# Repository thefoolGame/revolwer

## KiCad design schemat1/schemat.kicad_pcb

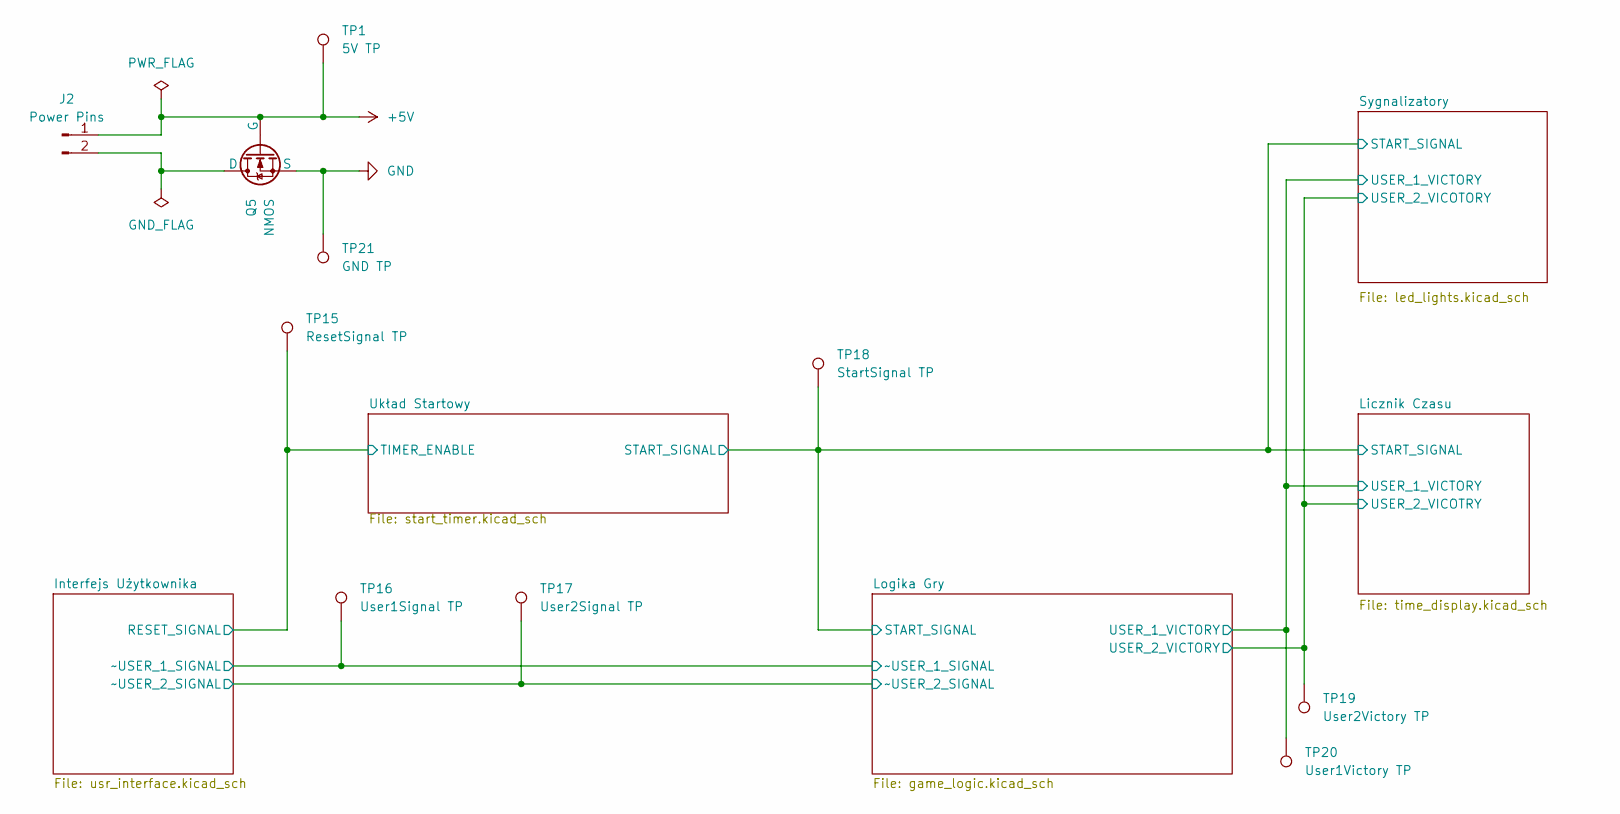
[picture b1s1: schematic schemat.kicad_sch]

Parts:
J2: Power Pins; Molex_KK-254_AE-6410-02A_1x02_P2.54mm_Vertical
Q5: NMOS; TO-220-3_Vertical
TP1: 5V TP; PinHeader_1x01_P2.54mm_Vertical
TP15: ResetSignal TP; PinHeader_1x01_P2.54mm_Vertical
TP16: User1Signal TP; PinHeader_1x01_P2.54mm_Vertical
TP17: User2Signal TP; PinHeader_1x01_P2.54mm_Vertical
TP18: StartSignal TP; PinHeader_1x01_P2.54mm_Vertical
TP19: User2Victory TP; PinHeader_1x01_P2.54mm_Vertical
TP20: User1Victory TP; PinHeader_1x01_P2.54mm_Vertical
TP21: GND TP; PinHeader_1x01_P2.54mm_Vertical

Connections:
+5V: J2.1, Q5.2 (G), TP1.1; also elsewhere on the board
/Interfejs Użytkownika/RESET_SIGNAL: TP15.1; also elsewhere on the board
/Interfejs Użytkownika/~USER_1_SIGNAL: TP16.1; also elsewhere on the board
/Interfejs Użytkownika/~USER_2_SIGNAL: TP17.1; also elsewhere on the board
/Licznik Czasu/START_SIGNAL: TP18.1; also elsewhere on the board
/Licznik Czasu/USER_1_VICTORY: TP20.1; also elsewhere on the board
/Licznik Czasu/USER_2_VICOTRY: TP19.1; also elsewhere on the board
GND: Q5.3 (S), TP21.1; also elsewhere on the board
unnamed: J2.2, Q5.1 (D)

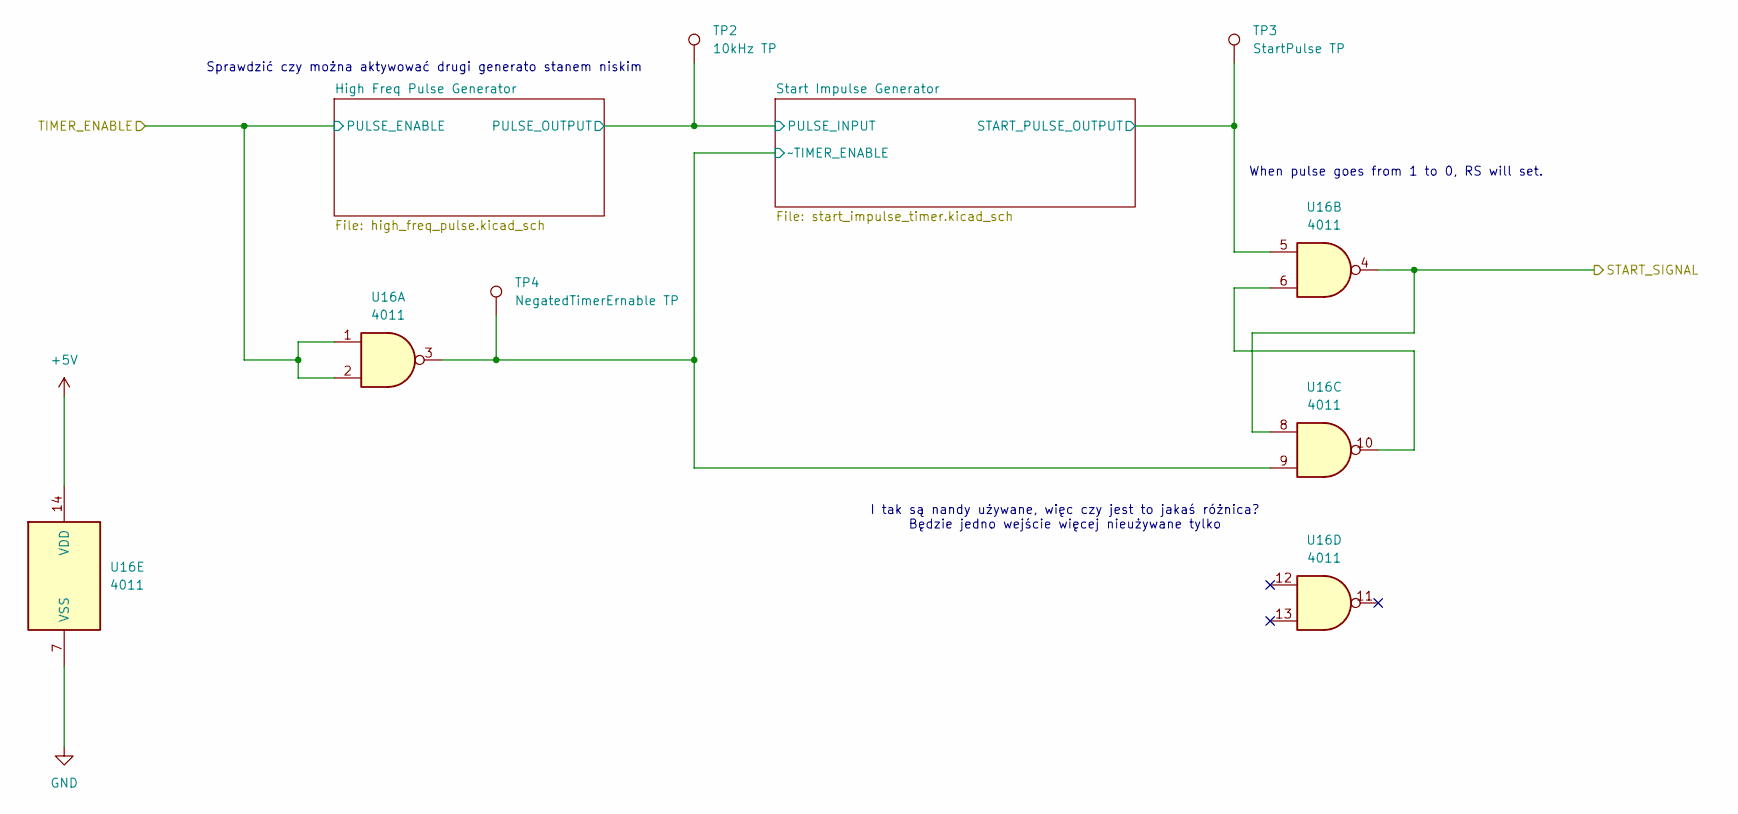
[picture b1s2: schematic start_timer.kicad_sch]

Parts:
TP2: 10kHz TP; PinHeader_1x01_P2.54mm_Vertical
TP3: StartPulse TP; PinHeader_1x01_P2.54mm_Vertical
TP4: NegatedTimerErnable TP; PinHeader_1x01_P2.54mm_Vertical
U16: 4011; DIP-14_W7.62mm

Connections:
+5V: U16.14 (VDD); also elsewhere on the board
/Interfejs Użytkownika/RESET_SIGNAL: U16.1, U16.2; also elsewhere on the board
/Licznik Czasu/START_SIGNAL: U16.4, U16.8; also elsewhere on the board
/Układ Startowy/High Freq Pulse Generator/PULSE_OUTPUT: TP2.1; also elsewhere on the board
/Układ Startowy/Start Impulse Generator/START_PULSE_OUTPUT: TP3.1, U16.5; also elsewhere on the board
/Układ Startowy/Start Impulse Generator/~TIMER_ENABLE: TP4.1, U16.3, U16.9; also elsewhere on the board
GND: U16.7 (VSS); also elsewhere on the board
unnamed: U16.6, U16.10

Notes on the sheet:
I tak są nandy używane, więc czy jest to jakaś różnica? Będzie jedno wejście więcej nieużywane tylko
Sprawdzić czy można aktywować drugi generato stanem niskim
When pulse goes from 1 to 0, RS will set.

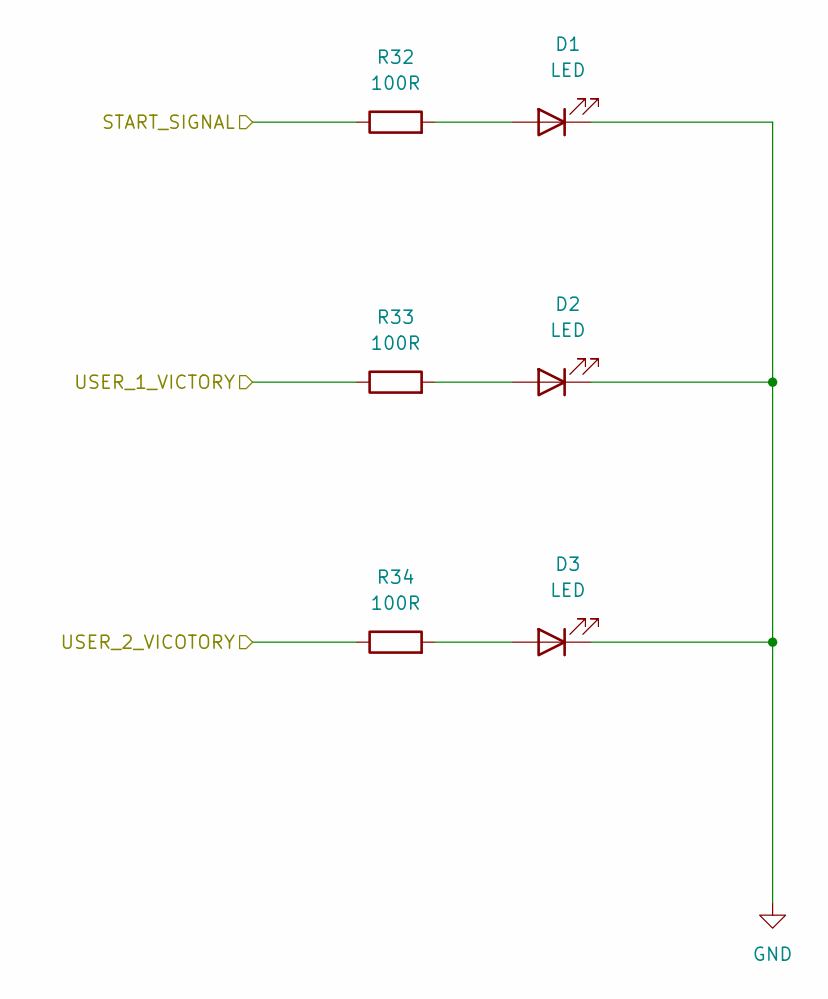
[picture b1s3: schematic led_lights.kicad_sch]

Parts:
D1, D2, D3: LED; LED_D4.0mm
R32, R33, R34: 100R; R_Axial_DIN0207_L6.3mm_D2.5mm_P10.16mm_Horizontal

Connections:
/Licznik Czasu/START_SIGNAL: R32.1; also elsewhere on the board
/Licznik Czasu/USER_1_VICTORY: R33.1; also elsewhere on the board
/Licznik Czasu/USER_2_VICOTRY: R34.1; also elsewhere on the board
GND: D1.1 (K), D2.1 (K), D3.1 (K); also elsewhere on the board
unnamed: D1.2 (A), R32.2
unnamed: D2.2 (A), R33.2
unnamed: D3.2 (A), R34.2

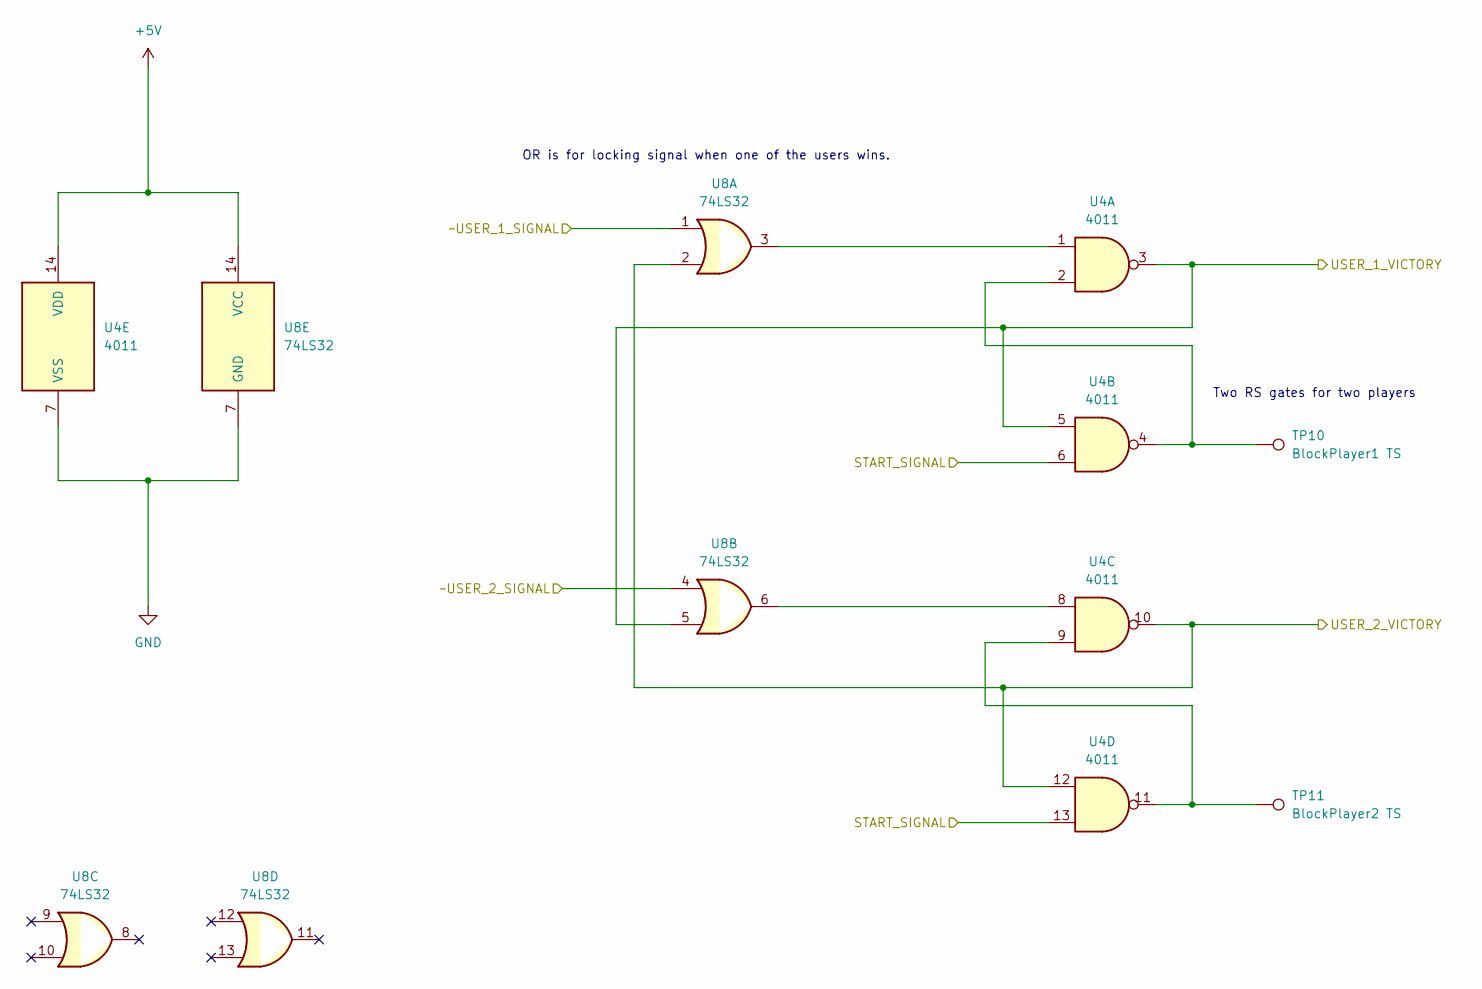
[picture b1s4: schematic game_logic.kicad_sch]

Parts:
TP10: BlockPlayer1 TS; PinHeader_1x01_P2.54mm_Vertical
TP11: BlockPlayer2 TS; PinHeader_1x01_P2.54mm_Vertical
U4: 4011; DIP-14_W7.62mm
U8: 74LS32; DIP-14_W7.62mm

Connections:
+5V: U4.14 (VDD), U8.14 (VCC); also elsewhere on the board
/Interfejs Użytkownika/~USER_1_SIGNAL: U8.1; also elsewhere on the board
/Interfejs Użytkownika/~USER_2_SIGNAL: U8.4; also elsewhere on the board
/Licznik Czasu/START_SIGNAL: U4.6, U4.13; also elsewhere on the board
/Licznik Czasu/USER_1_VICTORY: U4.3, U4.5, U8.5; also elsewhere on the board
/Licznik Czasu/USER_2_VICOTRY: U4.10, U4.12, U8.2; also elsewhere on the board
GND: U4.7 (VSS), U8.7 (GND); also elsewhere on the board
unnamed: TP10.1, U4.2, U4.4
unnamed: TP11.1, U4.9, U4.11
unnamed: U4.1, U8.3
unnamed: U4.8, U8.6

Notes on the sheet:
OR is for locking signal when one of the users wins.
Two RS gates for two players

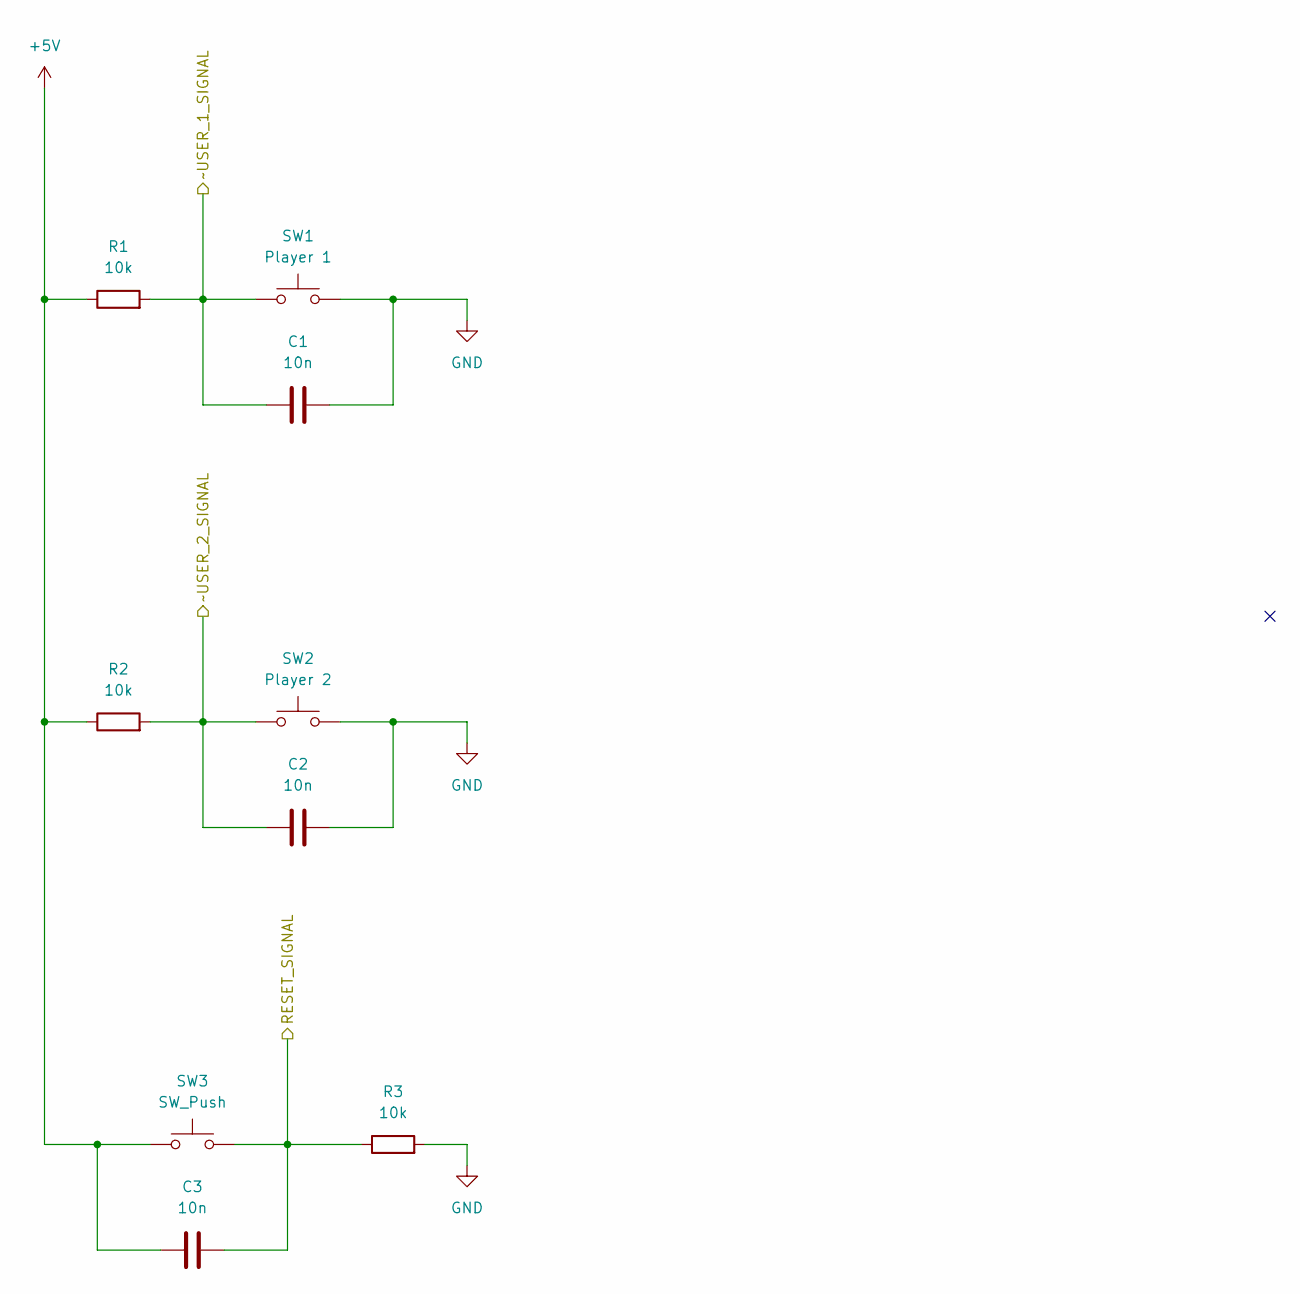
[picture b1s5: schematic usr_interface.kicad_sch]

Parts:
C1, C2, C3: 10n; C_Disc_D3.4mm_W2.1mm_P2.50mm
R1, R2, R3: 10k; R_Axial_DIN0207_L6.3mm_D2.5mm_P10.16mm_Horizontal
SW1: Player 1; SW_PUSH_6mm_H5mm
SW2: Player 2; SW_PUSH_6mm_H5mm
SW3: SW_Push; SW_PUSH_6mm_H5mm

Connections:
+5V: C3.1, R1.1, R2.1, SW3.1; also elsewhere on the board
/Interfejs Użytkownika/RESET_SIGNAL: C3.2, R3.1, SW3.2; also elsewhere on the board
/Interfejs Użytkownika/~USER_1_SIGNAL: C1.1, R1.2, SW1.1; also elsewhere on the board
/Interfejs Użytkownika/~USER_2_SIGNAL: C2.1, R2.2, SW2.1; also elsewhere on the board
GND: C1.2, C2.2, R3.2, SW1.2, SW2.2; also elsewhere on the board

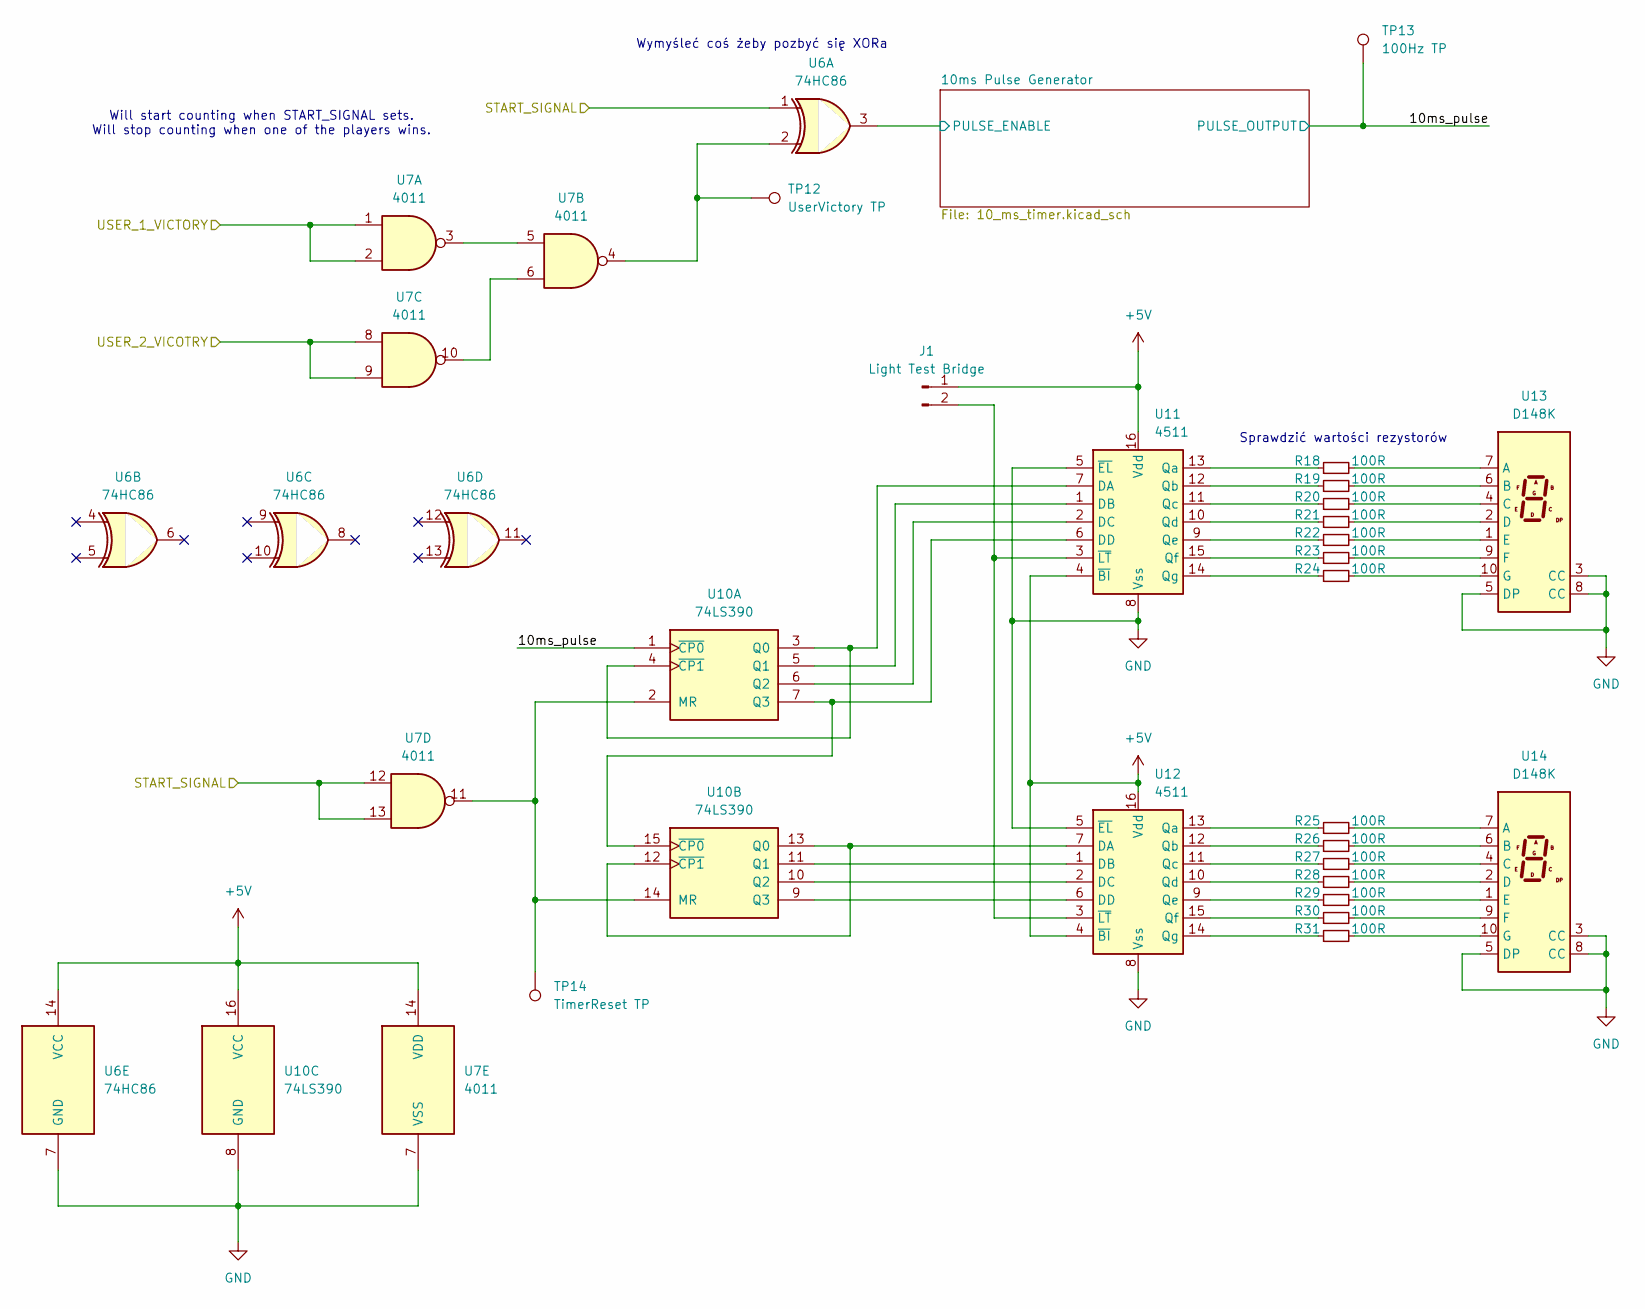
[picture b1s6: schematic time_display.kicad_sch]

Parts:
J1: Light Test Bridge; PinHeader_1x02_P2.54mm_Vertical
R18, R19, R20, R21, R22, R23, R24, R25, R26, R27, R28, R29, R30, R31: 100R; R_Axial_DIN0207_L6.3mm_D2.5mm_P10.16mm_Horizontal
TP12: UserVictory TP; PinHeader_1x01_P2.54mm_Vertical
TP13: 100Hz TP; PinHeader_1x01_P2.54mm_Vertical
TP14: TimerReset TP; PinHeader_1x01_P2.54mm_Vertical
U6: 74HC86; DIP-14_W7.62mm
U7: 4011; DIP-14_W7.62mm
U10: 74LS390; DIP-16_W7.62mm
U11, U12: 4511; DIP-16_W7.62mm
U13, U14: D148K; 7SegmentLED_LTS6760_LTS6780

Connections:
+5V: J1.1, U6.14 (VCC), U7.14 (VDD), U10.16 (VCC), U11.4 (~BI), U11.16 (Vdd), U12.4 (~BI), U12.16 (Vdd); also elsewhere on the board
/Licznik Czasu/10ms Pulse Generator/PULSE_ENABLE: U6.3; also elsewhere on the board
/Licznik Czasu/10ms_pulse: TP13.1, U10.1 (~CP0); also elsewhere on the board
/Licznik Czasu/START_SIGNAL: U6.1, U7.12, U7.13; also elsewhere on the board
/Licznik Czasu/USER_1_VICTORY: U7.1, U7.2; also elsewhere on the board
/Licznik Czasu/USER_2_VICOTRY: U7.8, U7.9; also elsewhere on the board
GND: U6.7 (GND), U7.7 (VSS), U10.8 (GND), U11.5 (~EL), U11.8 (Vss), U12.5 (~EL), U12.8 (Vss), U13.3 (CC), U13.5 (DP), U13.8 (CC), U14.3 (CC), U14.5 (DP), U14.8 (CC); also elsewhere on the board
unnamed: J1.2, U11.3 (~LT), U12.3 (~LT)
unnamed: TP12.1, U6.2, U7.4
unnamed: U7.3, U7.5
unnamed: U7.6, U7.10
unnamed: TP14.1, U7.11, U10.2 (MR), U10.14 (MR)
unnamed: U10.3 (Q0), U10.4 (~CP1), U11.7 (DA)
unnamed: U10.5 (Q1), U11.1 (DB)
unnamed: U10.6 (Q2), U11.2 (DC)
unnamed: U10.7 (Q3), U10.15 (~CP0), U11.6 (DD)
unnamed: U10.12 (~CP1), U10.13 (Q0), U12.7 (DA)
unnamed: U10.11 (Q1), U12.1 (DB)
unnamed: U10.10 (Q2), U12.2 (DC)
unnamed: U10.9 (Q3), U12.6 (DD)
unnamed: R18.1, U11.13 (Qa)
unnamed: R19.1, U11.12 (Qb)
unnamed: R20.1, U11.11 (Qc)
unnamed: R21.1, U11.10 (Qd)
unnamed: R22.1, U11.9 (Qe)
unnamed: R23.1, U11.15 (Qf)
unnamed: R24.1, U11.14 (Qg)
unnamed: R25.1, U12.13 (Qa)
unnamed: R26.1, U12.12 (Qb)
unnamed: R27.1, U12.11 (Qc)
unnamed: R28.1, U12.10 (Qd)
unnamed: R29.1, U12.9 (Qe)
unnamed: R30.1, U12.15 (Qf)
unnamed: R31.1, U12.14 (Qg)
unnamed: R18.2, U13.7 (A)
unnamed: R19.2, U13.6 (B)
unnamed: R20.2, U13.4 (C)
unnamed: R21.2, U13.2 (D)
unnamed: R22.2, U13.1 (E)
unnamed: R23.2, U13.9 (F)
unnamed: R24.2, U13.10 (G)
unnamed: R25.2, U14.7 (A)
unnamed: R26.2, U14.6 (B)
unnamed: R27.2, U14.4 (C)
unnamed: R28.2, U14.2 (D)
unnamed: R29.2, U14.1 (E)
unnamed: R30.2, U14.9 (F)
unnamed: R31.2, U14.10 (G)

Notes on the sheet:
Will start counting when START_SIGNAL sets. Will stop counting when one of the players wins.
Sprawdzić wartości rezystorów
Wymyśleć coś żeby pozbyć się XORa

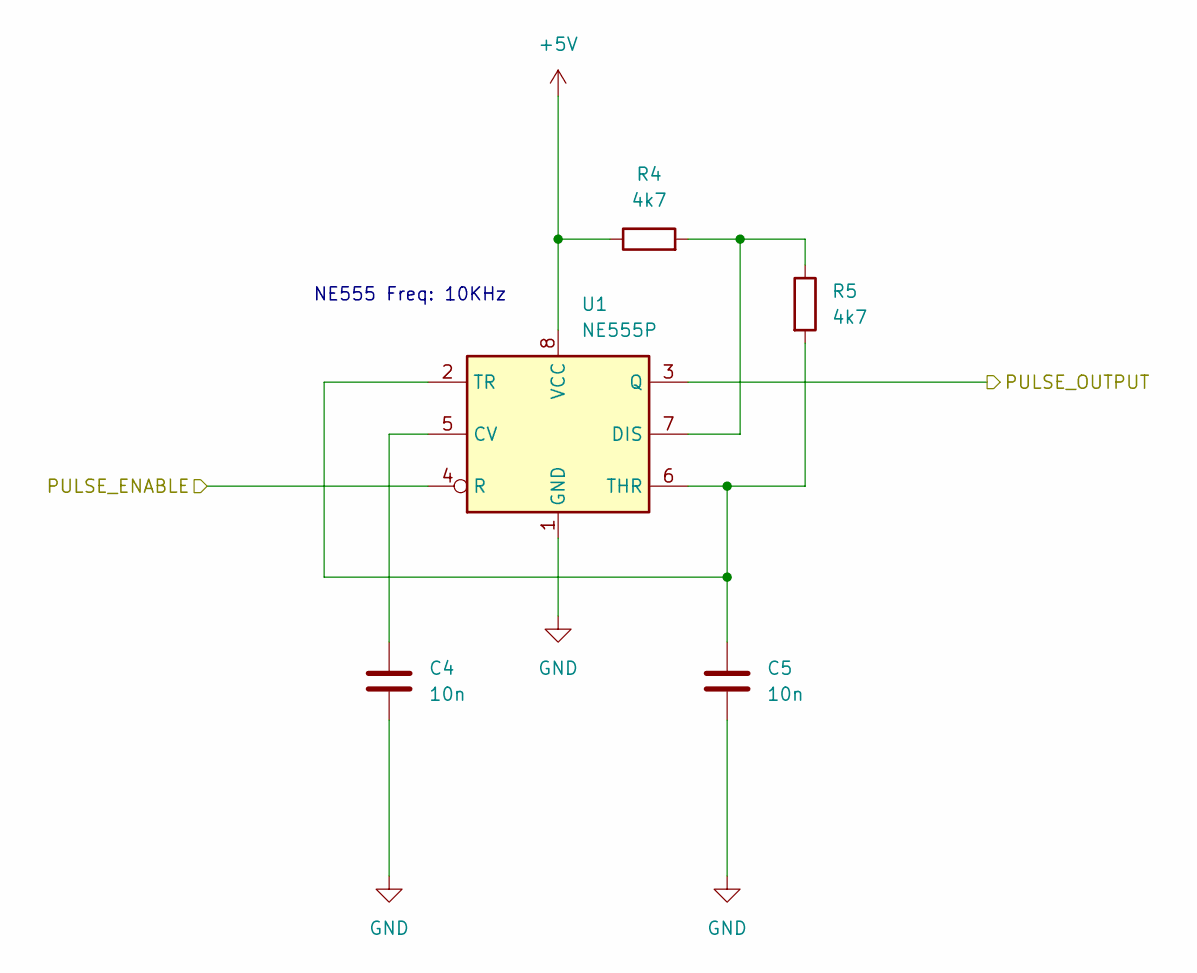
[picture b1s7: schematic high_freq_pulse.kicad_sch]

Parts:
C4, C5: 10n; C_Disc_D3.4mm_W2.1mm_P2.50mm
R4, R5: 4k7; R_Axial_DIN0207_L6.3mm_D2.5mm_P10.16mm_Horizontal
U1: NE555P; DIP-8_W7.62mm

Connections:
+5V: R4.1, U1.8 (VCC); also elsewhere on the board
/Interfejs Użytkownika/RESET_SIGNAL: U1.4 (R); also elsewhere on the board
/Układ Startowy/High Freq Pulse Generator/PULSE_OUTPUT: U1.3 (Q); also elsewhere on the board
GND: C4.2, C5.2, U1.1 (GND); also elsewhere on the board
unnamed: C4.1, U1.5 (CV)
unnamed: R4.2, R5.1, U1.7 (DIS)
unnamed: C5.1, R5.2, U1.2 (TR), U1.6 (THR)

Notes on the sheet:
NE555 Freq: 10KHz

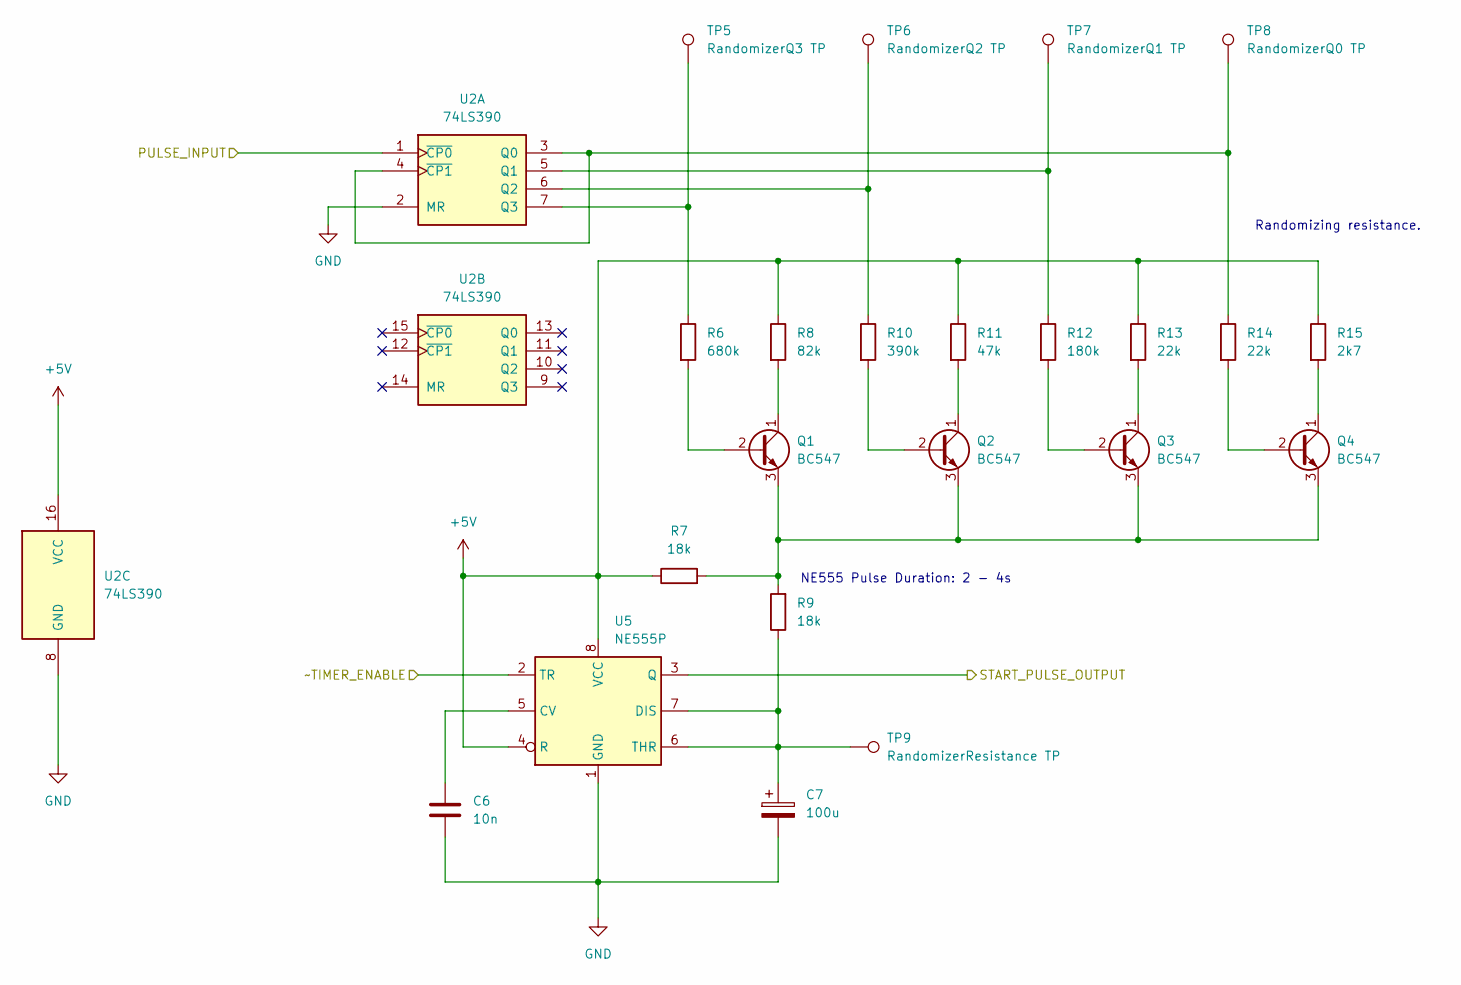
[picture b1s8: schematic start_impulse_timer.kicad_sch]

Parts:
C6: 10n; C_Disc_D3.4mm_W2.1mm_P2.50mm
C7: 100u; CP_Radial_D6.3mm_P2.50mm
Q1, Q2, Q3, Q4: BC547; TO-92
R6: 680k; R_Axial_DIN0207_L6.3mm_D2.5mm_P10.16mm_Horizontal
R7, R9: 18k; R_Axial_DIN0207_L6.3mm_D2.5mm_P10.16mm_Horizontal
R8: 82k; R_Axial_DIN0207_L6.3mm_D2.5mm_P10.16mm_Horizontal
R10: 390k; R_Axial_DIN0207_L6.3mm_D2.5mm_P10.16mm_Horizontal
R11: 47k; R_Axial_DIN0207_L6.3mm_D2.5mm_P10.16mm_Horizontal
R12: 180k; R_Axial_DIN0207_L6.3mm_D2.5mm_P10.16mm_Horizontal
R13, R14: 22k; R_Axial_DIN0207_L6.3mm_D2.5mm_P10.16mm_Horizontal
R15: 2k7; R_Axial_DIN0207_L6.3mm_D2.5mm_P10.16mm_Horizontal
TP5: RandomizerQ3 TP; PinHeader_1x01_P2.54mm_Vertical
TP6: RandomizerQ2 TP; PinHeader_1x01_P2.54mm_Vertical
TP7: RandomizerQ1 TP; PinHeader_1x01_P2.54mm_Vertical
TP8: RandomizerQ0 TP; PinHeader_1x01_P2.54mm_Vertical
TP9: RandomizerResistance TP; PinHeader_1x01_P2.54mm_Vertical
U2: 74LS390; DIP-16_W7.62mm
U5: NE555P; DIP-8_W7.62mm

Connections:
+5V: R7.1, R8.1, R11.1, R13.1, R15.1, U2.16 (VCC), U5.4 (R), U5.8 (VCC); also elsewhere on the board
/Układ Startowy/High Freq Pulse Generator/PULSE_OUTPUT: U2.1 (~CP0); also elsewhere on the board
/Układ Startowy/Start Impulse Generator/START_PULSE_OUTPUT: U5.3 (Q); also elsewhere on the board
/Układ Startowy/Start Impulse Generator/~TIMER_ENABLE: U5.2 (TR); also elsewhere on the board
GND: C6.2, C7.2, U2.2 (MR), U2.8 (GND), U5.1 (GND); also elsewhere on the board
unnamed: Q1.2 (B), R6.2
unnamed: Q1.1 (C), R8.2
unnamed: Q1.3 (E), Q2.3 (E), Q3.3 (E), Q4.3 (E), R7.2, R9.2
unnamed: Q2.2 (B), R10.2
unnamed: Q2.1 (C), R11.2
unnamed: Q3.2 (B), R12.2
unnamed: Q3.1 (C), R13.2
unnamed: Q4.2 (B), R14.2
unnamed: Q4.1 (C), R15.2
unnamed: R14.1, TP8.1, U2.3 (Q0), U2.4 (~CP1)
unnamed: R12.1, TP7.1, U2.5 (Q1)
unnamed: R10.1, TP6.1, U2.6 (Q2)
unnamed: R6.1, TP5.1, U2.7 (Q3)
unnamed: C6.1, U5.5 (CV)
unnamed: C7.1, R9.1, TP9.1, U5.6 (THR), U5.7 (DIS)

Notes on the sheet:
Randomizing resistance.
NE555 Pulse Duration: 2 - 4s

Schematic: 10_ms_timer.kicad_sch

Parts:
C8: 10n; C_Disc_D3.4mm_W2.1mm_P2.50mm
C9: 100n; C_Disc_D6.0mm_W2.5mm_P5.00mm
R16: 44k; R_Axial_DIN0207_L6.3mm_D2.5mm_P10.16mm_Horizontal
R17: 50k; R_Axial_DIN0207_L6.3mm_D2.5mm_P10.16mm_Horizontal
U3: NE555P; DIP-8_W7.62mm

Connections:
+5V: R16.1, U3.8 (VCC); also elsewhere on the board
/Licznik Czasu/10ms Pulse Generator/PULSE_ENABLE: U3.4 (R); also elsewhere on the board
/Licznik Czasu/10ms_pulse: U3.3 (Q); also elsewhere on the board
GND: C8.2, C9.2, U3.1 (GND); also elsewhere on the board
unnamed: C8.1, U3.5 (CV)
unnamed: R16.2, R17.1, U3.7 (DIS)
unnamed: C9.1, R17.2, U3.2 (TR), U3.6 (THR)

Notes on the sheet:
NE555 Freq: 100Hz

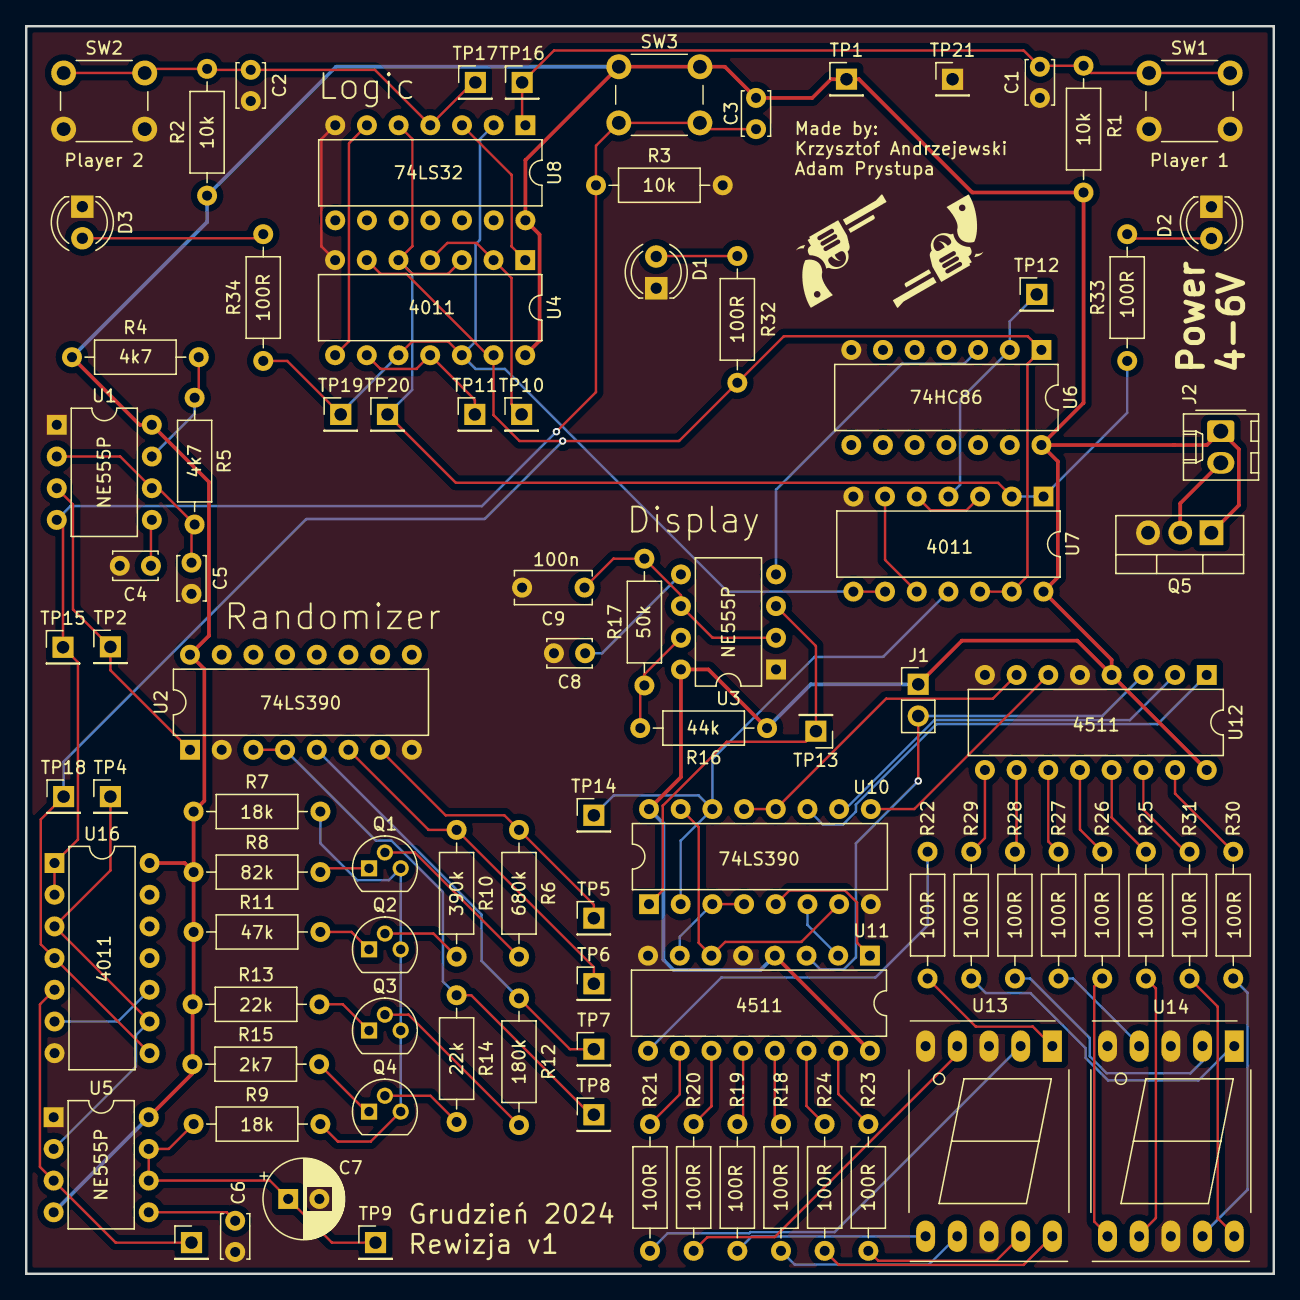
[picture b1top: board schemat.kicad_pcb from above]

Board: 2 copper layers, 100.0 x 100.0 mm, 91 parts (0 on the bottom side), 84 nets.

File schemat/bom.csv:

Reference,Value,Qty,DNP,,
,,,,,
"C1,C2,C3,C9",100n,4,,,
"C4,C8",1n,2,,,
"C5,C6,C7",10n,3,,,
"D1,D2,D3",LED,3,3,tht,
J1,Light Test Bridge,1,1,,
"Q1,Q2,Q3,Q4",BC547,4,4,tht,
"R1,R2,R3",10k,3,,,
"R4,R5",4k7,2,,,
R6,680k,1,,,
"R7,R9",18k,2,,,
R8,82k,1,,,
R10,390k,1,,,
R11,47k,1,,,
R12,180k,1,,,
"R13,R14",22k,2,,,
R15,2k7,1,,,
R16,44k,1,,,
R17,50k,1,,,
"R18,R19,R20,R21,R22,R23,R24,R25,R26,R27,R28,R29,R30,R31",100R,14,10,tht,
"R32,R33,R34",150R,3,,,
"SW1,SW2,SW3",SW_MEC_5E,3,3,tht,
"U1,U3,U5",NE555P,3,3,tht,v
"U2,U10",74LS390,2,,4017x3,
"U4,U7,U9",7400,3,3,4011 tht,v
U6,74HC86,1,1,tht,
U8,74LS32,1,1,tht,
"U11,U12",4511,2,2,tht,
"U13,U14",D148K,2,2,,

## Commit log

2024-12-05 dodano zabezpieczenie przeciwko odwrotnej polaryzacji
2024-12-05 zmiana elementu C7 na elektrolityczny, aktualizacja w schemacie i na pcb
2024-12-05 zmiana footprinta tranzystora w układzie zabezpieczającym przed przeciwną polaryzacją
2024-12-10 poprawione thermal reliefs
2024-12-12 poprawione schematy
2024-12-19 gerbery
